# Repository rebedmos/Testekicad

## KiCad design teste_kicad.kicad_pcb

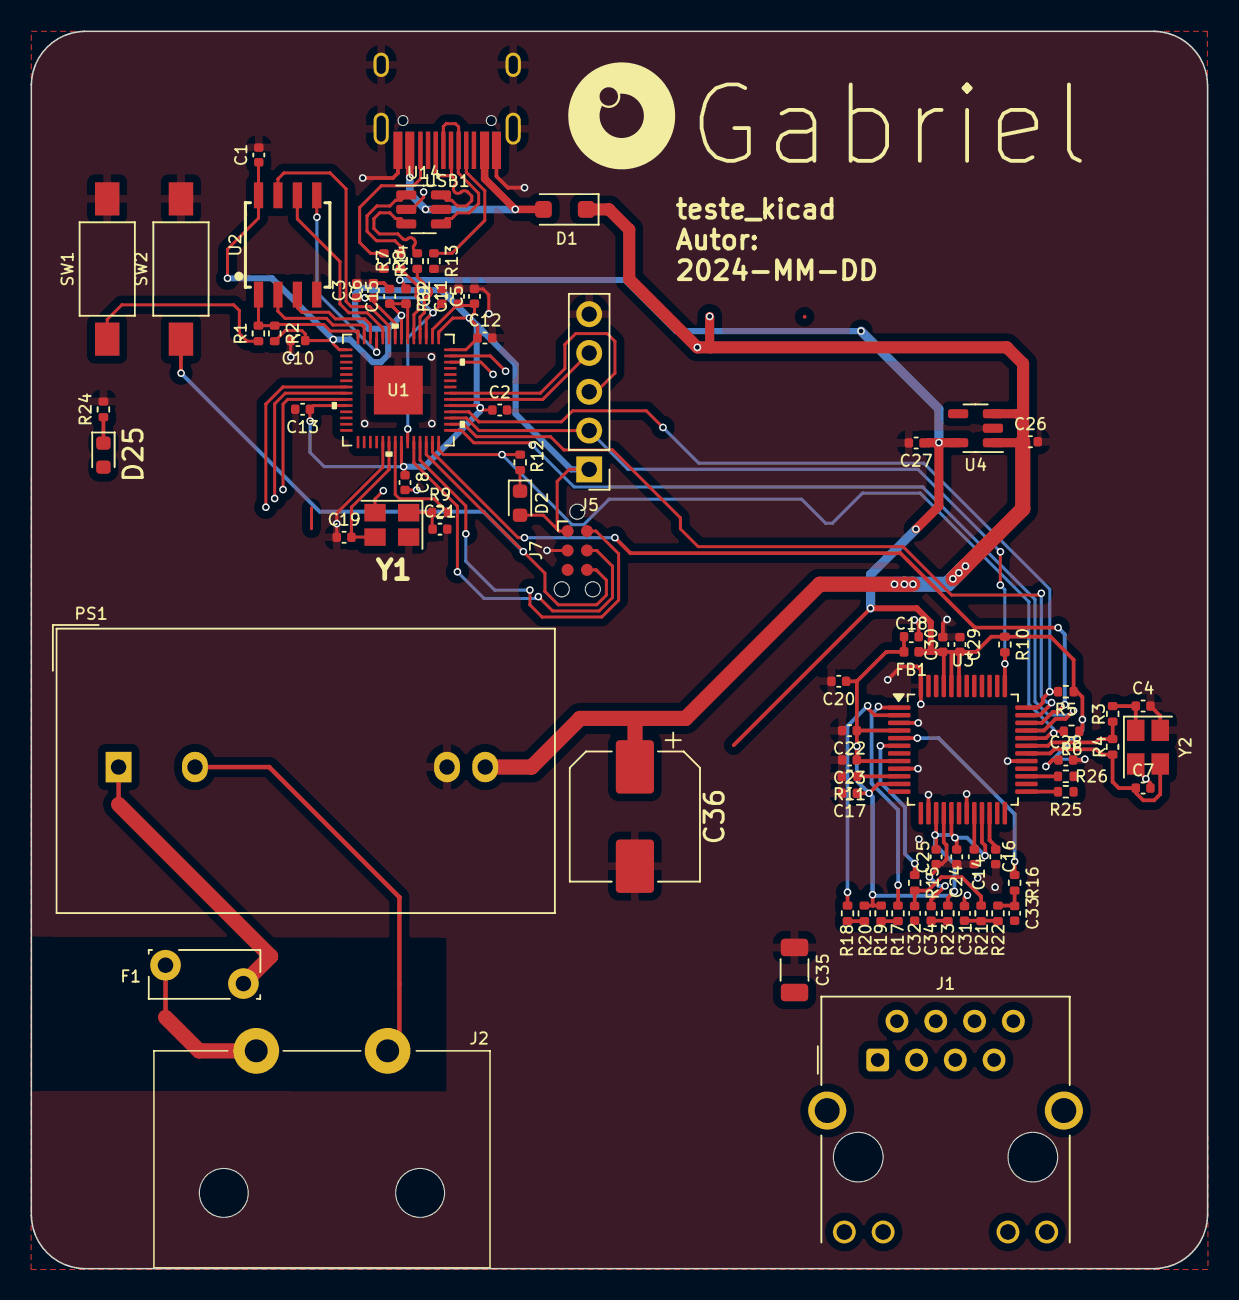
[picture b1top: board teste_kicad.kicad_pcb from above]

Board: 4 copper layers, 77.0 x 81.0 mm, 83 parts (0 on the bottom side), 64 nets.

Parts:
C1, C5, C6, C8, C9, C10, C11, C12, C13, C15: 100nF/6.3V; C_0402_1005Metric
C2, C3: 1uF/6.3V; C_0402_1005Metric
C4, C7: 18pF; C_0402_1005Metric
C14: 4.7uF; C_0402_1005Metric
C16, C18, C20, C22, C23, C24, C25, C28, C29, C31: 0.1uF; C_0402_1005Metric
C17, C26, C27, C30: 1uF; C_0402_1005Metric
C19, C21: C_Small; C_0402_1005Metric
C32, C33: 68nF; C_0402_1005Metric
C34: 22nF; C_0402_1005Metric
C35: 1nF/2kV; C_1206_3216Metric
C36: 220uF; CP_Elec_8x10
D1: PMEG2005EH; D_SOD-123F
D2, D25: LED; LED_0603_1608Metric
F1: FTR250-030; Fuse_Bourns_MF-RG300
FB1, FB2: FerriteBead_Small; L_0402_1005Metric
J1: RJ45_Hanrun_HR911105A_Horizontal
J2: Conn_01x02; DB-8-5DP9
J5: NOPOP; PinHeader_1x05_P2.54mm_Vertical
J7: Conn_01x06; Tag-Connect_TC2030-IDC-NL_2x03_P1.27mm_Vertical
PS1: HLK-2M05; Converter_ACDC_Hi-Link_HLK-2Mxx
R1, R9: 1k; R_0402_1005Metric
R2: NOPOP; R_0402_1005Metric
R3: 0R; R_0402_1005Metric
R4: 1M; R_0402_1005Metric
R5, R6, R10: 4k7; R_0402_1005Metric
R7, R8: 27R; R_0402_1005Metric
R11: 12k4/1%; R_0402_1005Metric
R12, R24, R25, R26: 330R; R_0402_1005Metric
R13, R14: 5k1; R_0402_1005Metric
R15, R16, R17, R18: 3R3; R_0402_1005Metric
R19, R20, R21, R22: 49R9; R_0402_1005Metric
R23: 10R; R_0402_1005Metric
SW1, SW2: NOPOP; SW_SPST_FSMSM
U1: RP2040
U2: W25Q32FVSS; SOIC-8
U3: W5500; LQFP-48_7x7mm_P0.5mm
U4: AP2112K-3.3; SOT-23-5
U14: USBLC6-2SC6; SOT-23-6
USB1: HRO-TYPE-C-31-M-12; HRO-TYPE-C-31-M-12-HandSoldering
Y1: 12MHz; Crystal_SMD_SeikoEpson_TSX3225-4Pin_3.2x2.5mm
Y2: 25MHz; Crystal_SMD_SeikoEpson_TSX3225-4Pin_3.2x2.5mm

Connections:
/ACTn: R26.2, U3.27 (ACTLED)
/INTn: R5.2, U1.32 (GPIO21), U3.36 (~INT)
/LINKn: R25.2, U3.25 (LINKLED)
/MAIN+3V3: C27.1, C28.1, C29.1, C30.1, D25.2 (A), FB1.1, FB2.1, J1.9, J1.12, R5.1, R6.1, R10.1, U3.43 (PMODE2), U3.44 (PMODE1), U3.45 (PMODE0), U4.5 (VOUT)
/MAIN+5V: C26.1, C36.1, D1.1 (K), PS1.4 (+Vout), U4.1 (VIN), U4.3 (EN)
/Microcontroller circuit/FLASH_3V3: C1.1, C2.1, C5.1, C8.1, C10.1, C11.1, C12.1, C13.1, C15.1, D2.2 (A), FB2.2, J5.1, J7.1, R2.2, U1.1 (IOVDD), U1.10 (IOVDD), U1.22 (IOVDD), U1.33 (IOVDD), U1.42 (IOVDD), U1.43 (ADC_AVDD), U1.44 (VREG_VIN), U1.48 (USB_VDD), U1.49 (IOVDD), U2.8 (VCC)
/Microcontroller circuit/GPIO22/SPI_SCK: J5.4, U1.34 (GPIO22)
/Microcontroller circuit/GPIO23/SPI_COPI: J5.3, U1.35 (GPIO23)
/Microcontroller circuit/QSPI_SCLK: U1.52 (QSPI_SCLK), U2.6 (SCK)
/Microcontroller circuit/QSPI_SD0: U1.53 (QSPI_SD0), U2.5 (SI(D0))
/Microcontroller circuit/QSPI_SD1: U1.55 (QSPI_SD1), U2.2 (SO(D1))
/Microcontroller circuit/QSPI_SD2: U1.54 (QSPI_SD2), U2.3 (~WP~(D2))
/Microcontroller circuit/QSPI_SD3: U1.51 (QSPI_SD3), U2.7 (~HOLD~(D3))
/Microcontroller circuit/QSPI_SS: R1.2, R2.1, U1.56 (QSPI_SS_N), U2.1 (~CS~)
/Microcontroller circuit/RP2040_1V1: C3.1, C6.1, C9.1, U1.23 (DVDD), U1.45 (VREG_VOUT), U1.50 (DVDD)
/Microcontroller circuit/RP2040_D+: R7.2, U14.1 (I/O1)
/Microcontroller circuit/RP2040_D-: R8.2, U14.3 (I/O2)
/Microcontroller circuit/RP2040_DN: U14.4 (I/O2), USB1.5 (DN2), USB1.7 (DN1)
/Microcontroller circuit/RP2040_DP: U14.6 (I/O1), USB1.6 (DP1), USB1.8 (DP2)
/Microcontroller circuit/RP2040_RUN: J7.6, SW2.1 (A), U1.26 (RUN)
/Microcontroller circuit/RP2040_SWCLK: J7.4, U1.24 (SWCLK)
/Microcontroller circuit/RP2040_SWDIO: J7.2, U1.25 (SWDIO)
/Microcontroller circuit/RP2040_USB_BOOT: R1.1, SW1.1 (A)
/Microcontroller circuit/RP2040_XIN: C19.2, U1.20 (XIN), Y1.3
/Microcontroller circuit/RP2040_XOUT: R9.2, U1.21 (XOUT)
/Microcontroller circuit/USB_DN: R8.1, U1.46 (USB_DM)
/Microcontroller circuit/USB_DP: R7.1, U1.47 (USB_DP)
/Microcontroller circuit/VUSB: D1.2 (A), U14.5 (VBUS), USB1.2 (VBUS), USB1.11 (VBUS)
/RSTn: J5.2, R10.2, U1.31 (GPIO20), U3.37 (~RST)
/SPI0_CSn: R6.2, R12.2, U1.28 (GPIO17), U3.32 (~SCS)
/SPI0_RX: U1.27 (GPIO16), U3.34 (MISO)
/SPI0_SCK: U1.29 (GPIO18), U3.33 (SCLK)
/SPI0_TX: U1.30 (GPIO19), U3.35 (MOSI)
/W5500_3V3A: C17.1, C18.1, C20.1, C22.1, C23.1, C24.1, C25.1, FB1.2, R19.2, R20.2, R23.2, U3.4 (AVDD), U3.8 (AVDD), U3.11 (AVDD), U3.15 (AVDD), U3.17 (AVDD), U3.21 (AVDD)
/XI: C7.1, R4.2, U3.30 (XI/CLKIN), Y2.3
/XO: R3.1, R4.1, U3.31 (XO)
GND: C1.2, C2.2, C3.2, C4.2, C5.2, C6.2, C7.2, C8.2, C9.2, C10.2, C11.2, C12.2, C13.2, C14.2, C15.2, C16.2, C17.2, C18.2, C19.1, C20.2, C21.2, C22.2, C23.2, C24.2, C25.2, C26.2, C27.2, C28.2, C29.2, C30.2, C31.2, C34.2, C35.1, C36.2, J5.5, J7.3, PS1.3 (-Vout), R11.2, R13.2, R14.2, R24.2, SW1.2 (B), SW2.2 (B), U1.19 (TESTEN), U1.57 (GND), U2.4 (GND), U3.3 (AGND), U3.9 (AGND), U3.14 (AGND), U3.16 (AGND), U3.19 (AGND), U3.29 (GND), U3.48 (AGND), U4.2 (GND), U14.2 (GND), USB1.1 (GND), USB1.12 (GND), USB1.13 (SHIELD), Y1.2, Y1.4, Y2.2, Y2.4
GNDPWR: C35.2, J1.8, J1.SH
unnamed: C4.1, R3.2, Y2.1
unnamed: C21.1, R9.1, Y1.1
unnamed: C32.1, R15.2, R21.2
unnamed: C33.1, R16.2, R22.2
unnamed: D2.1 (K), R12.1
unnamed: D25.1 (K), R24.1
unnamed: J1.10, R26.1
unnamed: J1.11, R25.1
unnamed: C31.1, J1.5 (RCT), R21.1, R22.1
unnamed: C32.2, J1.3 (RD+)
unnamed: C33.2, J1.6 (RD-)
unnamed: C34.1, J1.4 (TCT), R23.1
unnamed: J1.1 (TD+), R18.2, R20.1
unnamed: J1.2 (TD-), R17.2, R19.1
unnamed: J2.1, PS1.2 (AC/N)
unnamed: F1.1, J2.2
unnamed: F1.2, PS1.1 (AC/L)
unnamed: C16.1, U3.22 (1V2O)
unnamed: R11.1, U3.10 (EXRES1)
unnamed: R16.1, U3.5 (RXN)
unnamed: R15.1, U3.6 (RXP)
unnamed: C14.1, U3.20 (TOCAP)
unnamed: R17.1, U3.1 (TXN)
unnamed: R18.1, U3.2 (TXP)
unnamed: R13.1, USB1.4 (CC1)
unnamed: R14.1, USB1.10 (CC2)

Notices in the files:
parts and their libraries:
Copyright 2021 Accelerated Designs. All rights reserved.
